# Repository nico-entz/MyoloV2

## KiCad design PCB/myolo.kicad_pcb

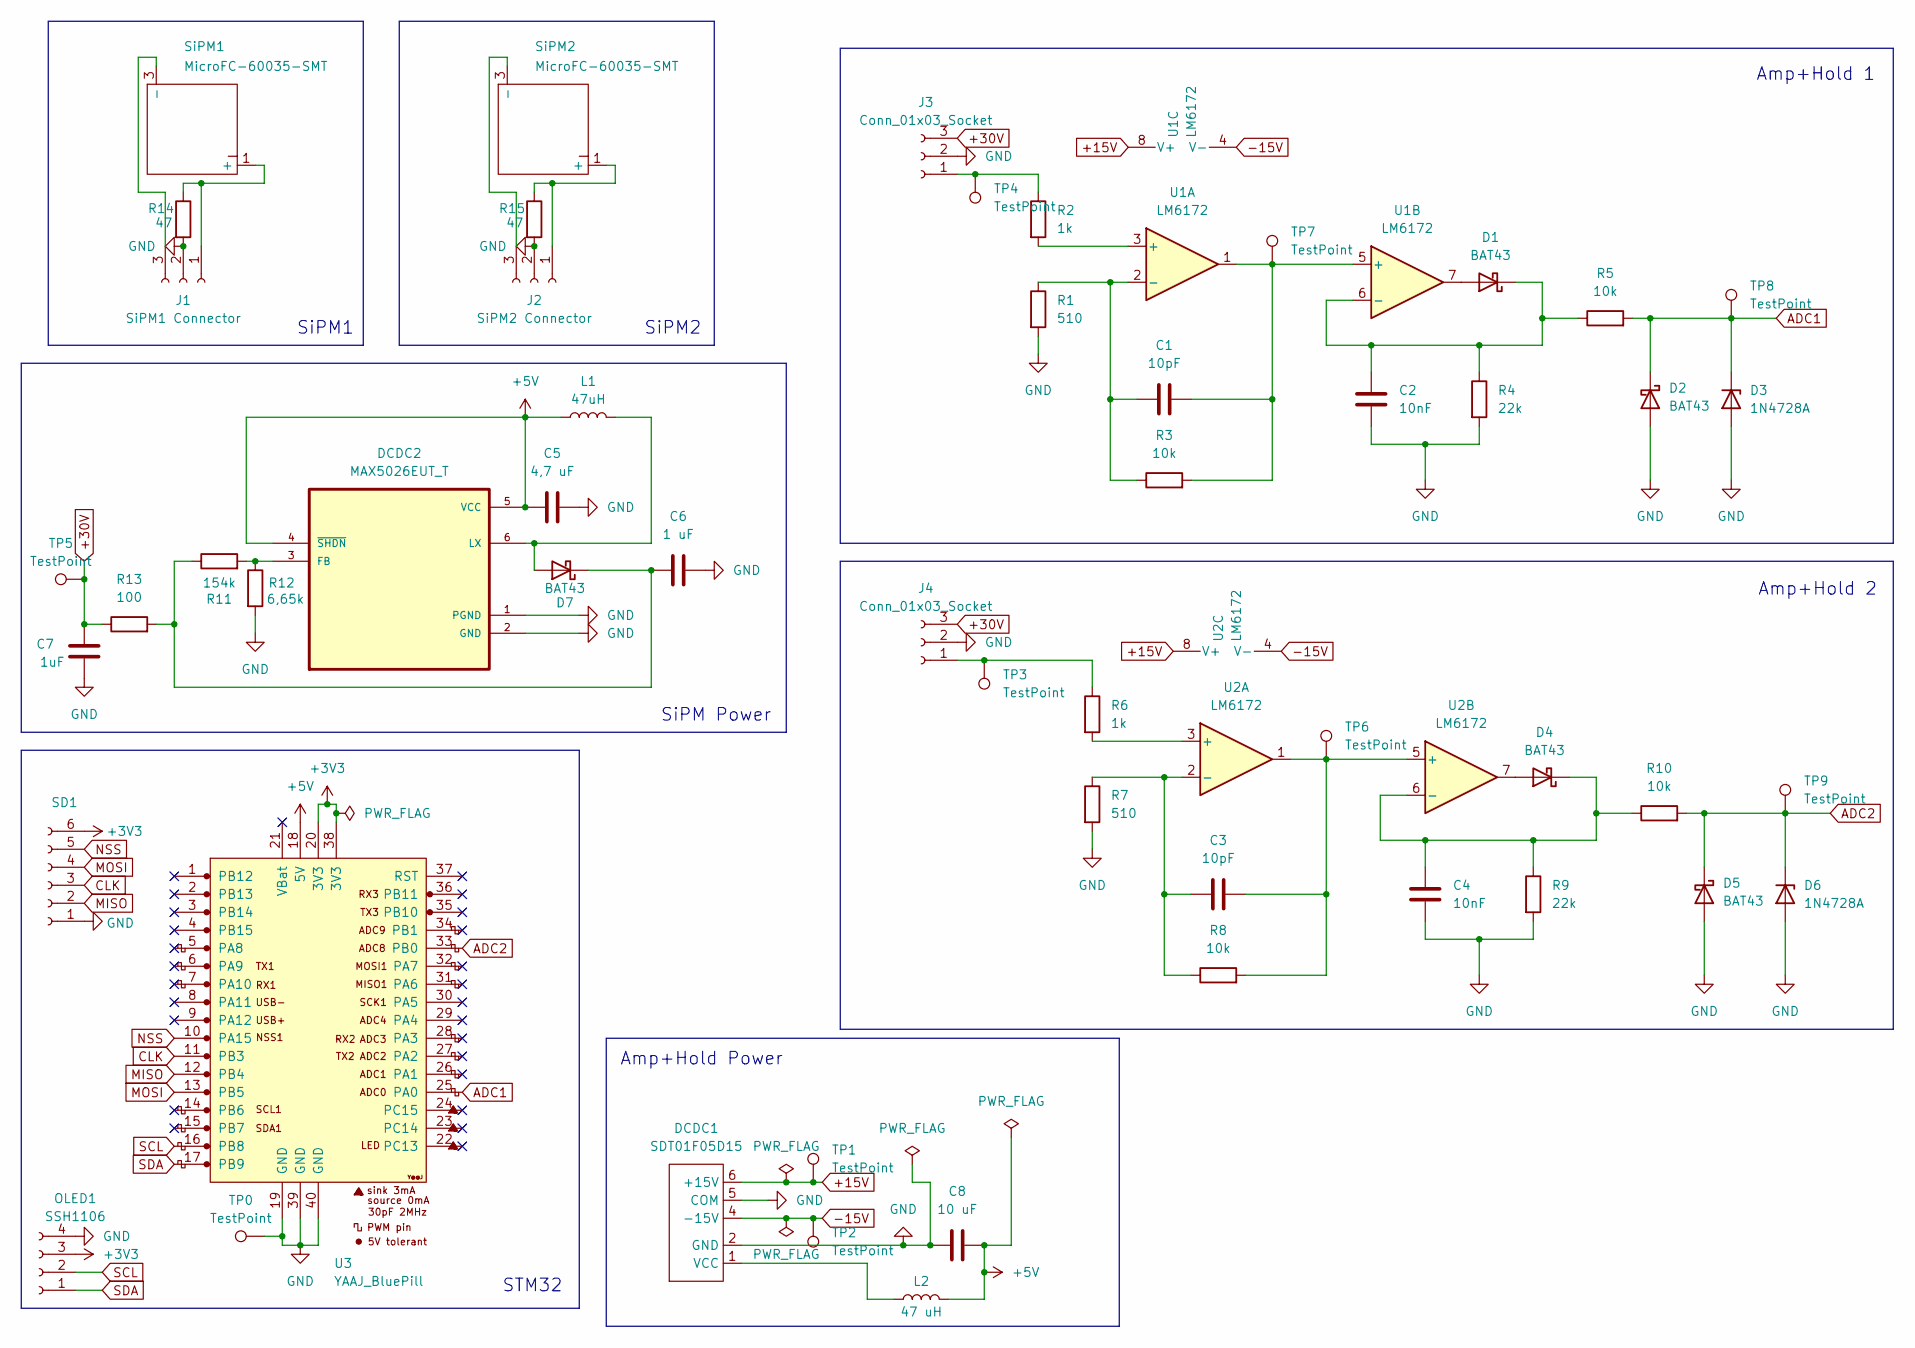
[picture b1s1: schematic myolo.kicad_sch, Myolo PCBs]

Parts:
C1, C3: 10pF; C_Disc_D5.0mm_W2.5mm_P2.50mm
C2, C4: 10nF; C_Disc_D5.0mm_W2.5mm_P2.50mm
C5: 4,7 uF; C_Disc_D5.0mm_W2.5mm_P2.50mm
C6: 1 uF; C_Disc_D5.0mm_W2.5mm_P2.50mm
C7: 1uF; C_Disc_D5.0mm_W2.5mm_P2.50mm
C8: 10 uF; C_Disc_D5.0mm_W2.5mm_P2.50mm
D1, D2, D4, D5, D7: BAT43; D_DO-34_SOD68_P7.62mm_Horizontal
D3, D6: 1N4728A; D_DO-34_SOD68_P7.62mm_Horizontal
DCDC1: SDT01F05D15; 1x6 NoGND
DCDC2: MAX5026EUT_T; MAX5026EU-T
J1: SiPM1 Connector; PinSocket_1x03_P2.54mm_Vertical_NoGND
J2: SiPM2 Connector; PinSocket_1x03_P2.54mm_Vertical_NoGND
J3, J4: Conn_01x03_Socket; PinSocket_1x03_P2.54mm_Vertical_NoGND
L1: 47uH; L_Axial_L5.3mm_D2.2mm_P7.62mm_Horizontal_Vishay_IM-1
L2: 47 uH; L_Axial_L5.3mm_D2.2mm_P7.62mm_Horizontal_Vishay_IM-1
OLED1: SSH1106; 1x04 NoGND
R1, R7: 510; R_Axial_DIN0204_L3.6mm_D1.6mm_P7.62mm_Horizontal
R2, R6: 1k; R_Axial_DIN0204_L3.6mm_D1.6mm_P7.62mm_Horizontal
R3, R5, R8, R10: 10k; R_Axial_DIN0204_L3.6mm_D1.6mm_P7.62mm_Horizontal
R4, R9: 22k; R_Axial_DIN0204_L3.6mm_D1.6mm_P7.62mm_Horizontal
R11: 154k; R_Axial_DIN0204_L3.6mm_D1.6mm_P7.62mm_Horizontal
R12: 6,65k; R_Axial_DIN0204_L3.6mm_D1.6mm_P7.62mm_Horizontal
R13: 100; R_Axial_DIN0204_L3.6mm_D1.6mm_P7.62mm_Horizontal
R14, R15: 47; R_Axial_DIN0204_L3.6mm_D1.6mm_P7.62mm_Horizontal
SD1: SDBrOut; SdHEAD
SiPM1, SiPM2: MicroFC-60035-SMT; SiPM3
TP0, TP1, TP2, TP3, TP4, TP5, TP6, TP7, TP8, TP9: TestPoint; TestPoint_Pad_1.0x1.0mm
U1, U2: LM6172; DIP-8_W10.16mm
U3: YAAJ_BluePill; BluePill

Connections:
+3V3: OLED1.3, SD1.6, U3.20 (3V3), U3.38 (3V3)
+5V: C5.1, C8.1, DCDC2.4 (~SHDN), DCDC2.5 (VCC), L1.1, L2.2, U3.18 (5V)
+15V: DCDC1.6 (+15V), TP1.1, U1.8 (V+), U2.8 (V+)
+30V: C7.1, J3.3, J4.3, R13.1, TP5.1
-15V: DCDC1.4 (-15V), TP2.1, U1.4 (V-), U2.4 (V-)
ADC1: D2.1 (K), D3.1 (K), R5.2, TP8.1, U3.25 (PA0)
ADC2: D5.1 (K), D6.1 (K), R10.2, TP9.1, U3.33 (PB0)
CLK: SD1.3, U3.11 (PB3)
GND: C2.2, C4.2, C5.2, C6.2, C7.2, C8.2, D2.2 (A), D3.2 (A), D5.2 (A), D6.2 (A), DCDC1.2 (GND), DCDC1.5 (COM), DCDC2.1 (PGND), DCDC2.2 (GND), J1.2, J2.2, J3.2, J4.2, OLED1.4, R1.2, R4.2, R7.2, R9.2, R12.2, R14.2, R15.2, SD1.1, TP0.1, U3.19 (GND), U3.39 (GND), U3.40 (GND)
MISO: SD1.2, U3.12 (PB4)
MOSI: SD1.4, U3.13 (PB5)
NSS: SD1.5, U3.10 (PA15)
unnamed: D1.2 (A), U1.7
unnamed: C2.1, D1.1 (K), R4.1, R5.1, U1.6 (-)
unnamed: D4.2 (A), U2.7
unnamed: C4.1, D4.1 (K), R9.1, R10.1, U2.6 (-)
unnamed: D7.2 (A), DCDC2.6 (LX), L1.2
unnamed: C6.1, D7.1 (K), R11.1, R13.2
unnamed: DCDC1.1 (VCC), L2.1
unnamed: DCDC2.3 (FB), R11.2, R12.1
unnamed: J1.1, R14.1, SiPM1.1 (+)
unnamed: J1.3, SiPM1.3 (-)
unnamed: J2.1, R15.1, SiPM2.1 (+)
unnamed: J2.3, SiPM2.3 (-)
unnamed: J3.1, R2.1, TP4.1
unnamed: J4.1, R6.1, TP3.1
unnamed: R2.2, U1.3 (+)
unnamed: C1.1, R1.1, R3.1, U1.2 (-)
unnamed: C1.2, R3.2, TP7.1, U1.1, U1.5 (+)
unnamed: R6.2, U2.3 (+)
unnamed: C3.1, R7.1, R8.1, U2.2 (-)
unnamed: C3.2, R8.2, TP6.1, U2.1, U2.5 (+)
SCL: OLED1.2, U3.16 (PB8)
SDA: OLED1.1, U3.17 (PB9)

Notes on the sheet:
Amp+Hold Power
SiPM2
SiPM Power
STM32
Amp+Hold 2
SiPM1
Amp+Hold 1

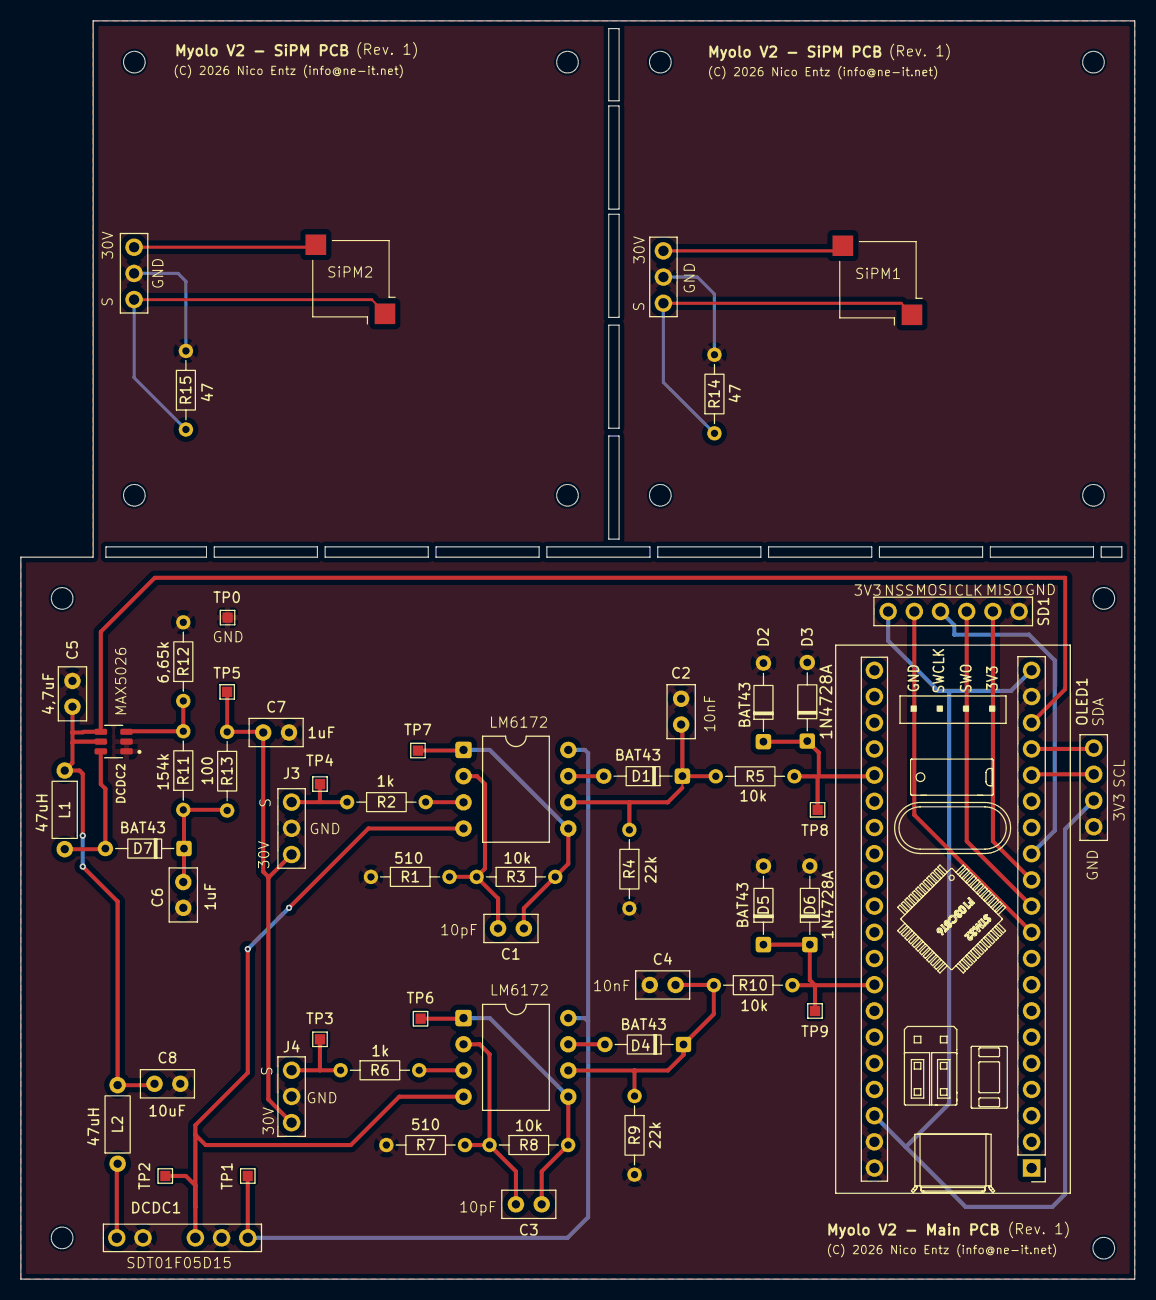
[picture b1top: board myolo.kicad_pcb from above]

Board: 2 copper layers, 108.0 x 122.0 mm, 55 parts (0 on the bottom side), 34 nets.

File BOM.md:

# Myonendetektor Bauteile & Werkzeuge
In dieser Liste finden Sie alle benötigten Bauteile und Werkzeuge, um selbst einen Myonendetektor zu bauen.
# Bauteile
## Spezialbauteile
### Platine
Platinenset **direkt** bestellen: [https://aisler.net/p/DRWNQMMB](https://aisler.net/p/DRWNQMMB)

KiCAD-Dateien für Platinenset: https://github.com/nico-entz/MyoloV2/tree/main/PCB

###  Szintillatoren
Szintillatoren (BC408 / 5x5x1cm) direkt bestellen (**2x**): https://www.ebay.de/itm/264903211281

Vorschläge für alternative Bezugsquellen sind jederzeit willkommen.
### Mikrocontroller
|Bezeichnung auf Platine / Schaltplan |   Typ       | Anzahl
|---------------------|----------------------------------|-------------------------------|
|U3                   | BluePill-Board mit STM32F103C6T8 | 1
| zur Programmierung  | ST-Link v2        						    | 1
BluePill-Board und STLink finden Sie auf gängigen Plattformen, z.B.  

ebay: https://www.ebay.de/itm/406405705535 (BluePill) | https://www.ebay.de/itm/116898601926 (ST-Link)

Amazon: https://www.amazon.de/dp/B077MJKCVT (BluePill) | https://www.amazon.de/dp/B07QBLNDPM (ST-Link)

## Kleinteile
### Lichtdetektoren / SiPM
|Bezeichnung auf Platine / Schaltplan |   Typ    | Anzahl
|----------------|-------------------------------|-------------------------------|
|SiPM1, SiPM2    | MICROFC-60035-SMT-TR          | 2        
### Spannungswandler
|Bezeichnung auf Platine / Hinweis |   Typ    | Anzahl
|----------------|-------------------------------|-------------------------------|
|DCDC1           | SDT01F05D15                   | 1
|DCDC2           | MAX5026EU_T    							 | 1

### Operationsverstärker
|Bezeichnung auf Platine / Schaltplan |   Typ    | Anzahl
|----------------|-------------------------------|-------------------------------|
|U1, U2          | LM6172                        | 2

### Widerstände
|Bezeichnung auf Platine / Schaltplan |   Wert   | Anzahl
|----------------|-------------------------------|-------------------------------|
|R1, R7          | 510 Ohm                       | 2
|R2, R6          | 1 kOhm                        | 2
|R3, R5, R8, R10 | 10 kOhm                       | 4
|R4, R9          | 22 kOhm                       | 2
|R11             | 154 kOhm                      | 1
|R12             | 6,65 kOhm                     | 1
|R13             | 100 Ohm                       | 1
|R14, R15        | 47 Ohm                        | 2    

### Kondensatoren
|Bezeichnung auf Platine / Schaltplan |   Wert   | Anzahl
|----------------|-------------------------------|-------------------------------|
|C1, C3          | 10 pF                         | 2 
|C2, C4          | 10 nF                         | 2
|C5              | 4,7 uF                        | 1
|C6, C7          | 1 uF                          | 2
|C8              | 10 uF                         | 1

### Dioden
|Bezeichnung auf Platine / Schaltplan |Typ       | Anzahl
|-------------------|----------------------------|-------------------------------|
|D1, D2, D4, D5, D7 | BAT43                      | 5 
|D3, D6             | 1N4728A                    | 2

### Spulen / Induktivitäten
|Bezeichnung auf Platine / Schaltplan |Wert       | Anzahl
|-------------------|----------------------------|-------------------------------|
|L1, L2             | 47 uF                      | 2

# Verbrauchsmaterial
- Teflonband aus dem Sanitärbereich (z.B. https://www.amazon.de/dp/B09GM4F8T8)
- Schwarzes Isolierband aus dem Elektronikbereich (z.B. https://www.amazon.de/dp/B0GBWG8949)
- Lötzinn, möglichst fein (z.B. 0,38mm Durchmesser) (z.B. https://www.digikey.de/de/products/detail/chip-quik-inc/SMDS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
- Schleifpapier (z.B. https://www.amazon.de/dp/B0DLWW9518)
- Silikonöl (z.B. https://www.amazon.de/dp/B089SQCN5G)
- verschiedenfarbige dünne Kabel (Litze) (z.B. https://www.amazon.de/dp/B07TV54V2T)
# Werkzeuge
 - Lötkolben
 - Heißluftpistole
 - Pinzette (optional)

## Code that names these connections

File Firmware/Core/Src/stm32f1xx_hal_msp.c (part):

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
    __HAL_RCC_GPIOA_CLK_ENABLE();
    /**ADC1 GPIO Configuration
    PA0-WKUP     ------> ADC1_IN0
    */
    GPIO_InitStruct.Pin = GPIO_PIN_0;
    GPIO_InitStruct.Mode = GPIO_MODE_ANALOG;
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
    __HAL_RCC_GPIOB_CLK_ENABLE();
    /**ADC2 GPIO Configuration
    PB0     ------> ADC2_IN8
    */
    GPIO_InitStruct.Pin = GPIO_PIN_0;
    GPIO_InitStruct.Mode = GPIO_MODE_ANALOG;
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    __HAL_RCC_ADC1_CLK_DISABLE();

    /**ADC1 GPIO Configuration
    PA0-WKUP     ------> ADC1_IN0
    */
    HAL_GPIO_DeInit(GPIOA, GPIO_PIN_0);

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    __HAL_RCC_ADC2_CLK_DISABLE();

    /**ADC2 GPIO Configuration
    PB0     ------> ADC2_IN8
    */
    HAL_GPIO_DeInit(GPIOB, GPIO_PIN_0);

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
    __HAL_RCC_GPIOB_CLK_ENABLE();
    /**SPI1 GPIO Configuration
    PB3     ------> SPI1_SCK
    PB4     ------> SPI1_MISO
    PB5     ------> SPI1_MOSI
    */
    GPIO_InitStruct.Pin = GPIO_PIN_3|GPIO_PIN_5;
    GPIO_InitStruct.Mode = GPIO_MODE_AF_PP;
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    __HAL_RCC_SPI1_CLK_DISABLE();

    /**SPI1 GPIO Configuration
    PB3     ------> SPI1_SCK
    PB4     ------> SPI1_MISO
    PB5     ------> SPI1_MOSI
    */
    HAL_GPIO_DeInit(GPIOB, GPIO_PIN_3|GPIO_PIN_4|GPIO_PIN_5);

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
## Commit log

2025-12-30 added PCB files
2025-12-30 changed text on board
2025-12-30 updated schematics settings
2025-12-30 deleted unnecessary files
2025-12-30 added schematics pdf
2026-01-05 Widerstandswerte angepasst
2026-01-06 changed license copyright
2026-01-07 added firmware
2026-01-14 code optimizations
2026-01-17 added bom
2026-01-17 added Fehlersuche.md
2026-01-17 added GND test point to pcb
2026-01-17 added myolo backups
2026-01-17 added debug oscilloscope screenshots
2026-01-17 debug document
2026-01-17 changes to debug document
2026-01-17 Update BOM.md
    updated pcb link
2026-01-17 Update BOM.md
    updated bom
2026-01-18 added webtools
2026-01-18 added python scripts
2026-01-18 added videos
2026-01-18 removed videos
2026-01-18 Update BOM.md
    added silicon oil url
2026-01-18 Update BOM.md
    added kicad files
2026-01-18 Update BOM.md
    fixed typo
2026-01-26 updated pcb
2026-01-26 updated graphics
2026-02-16 Update BOM.md
    updated product links
2026-03-06 Corrected inductor value from 47 uF to 47 uH
2026-03-07 Update BOM.md
    updated supply infos
2026-03-07 Update BOM.md
    supplier infos
2026-03-07 Update BOM.md
    added specification
2026-03-07 Update BOM.md
    fixed layout
2026-03-07 Update BOM.md
    added supplier
2026-03-07 Update BOM.md
    updated supplier link
2026-03-30 Update BOM.md
    Added Display & SD-Breakout
2026-04-07 Update BOM.md
    Added second Scintillator ebay link

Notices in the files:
Firmware/Core/Src/stm32f1xx_hal_msp.c:
Copyright (c) 2025 STMicroelectronics.
All rights reserved.
This software is licensed under terms that can be found in the LICENSE file
PCB/myolo.kicad_pcb:
(C) 2026 Nico Entz (info@ne-it.net)
